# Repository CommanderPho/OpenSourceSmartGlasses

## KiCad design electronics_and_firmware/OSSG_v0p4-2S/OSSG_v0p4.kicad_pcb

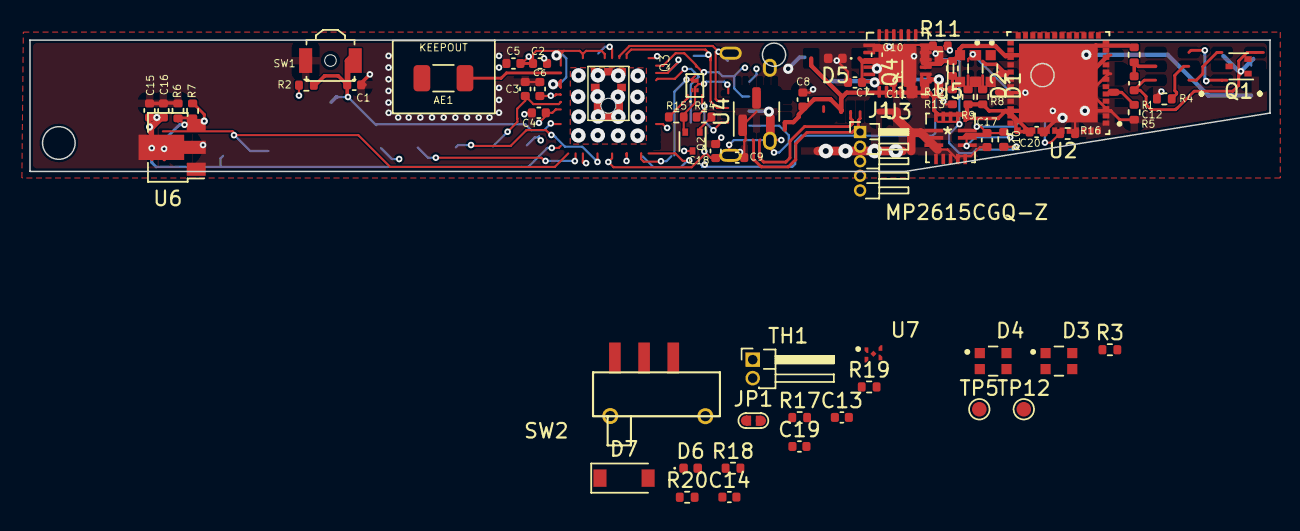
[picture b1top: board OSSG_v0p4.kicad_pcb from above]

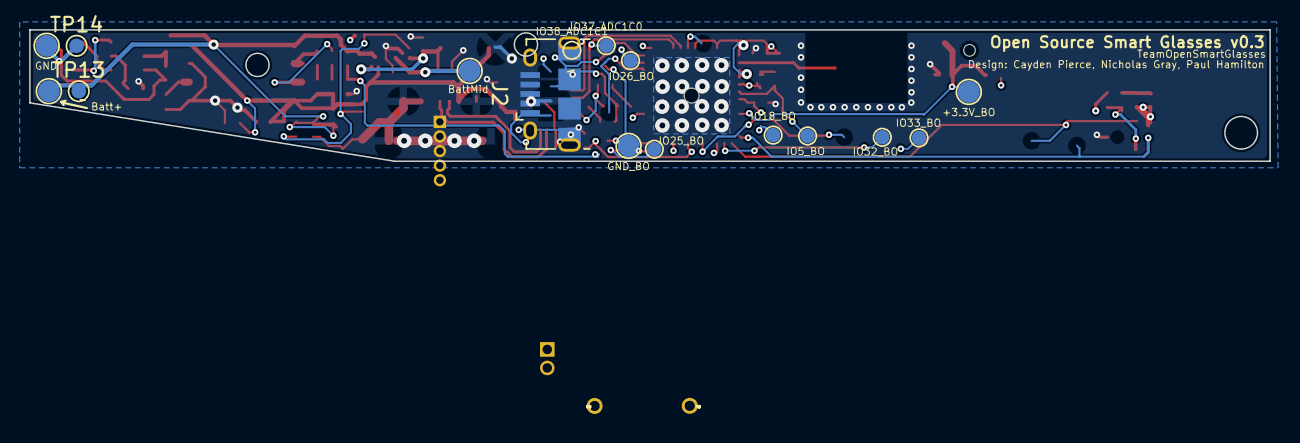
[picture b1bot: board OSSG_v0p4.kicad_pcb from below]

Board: 4 copper layers, 85.0 x 9.0 mm, 82 parts (16 on the bottom side), 54 nets.

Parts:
AE1: ANT3216LL00R2400A
C1, C12: 100nF; C_0402_1005Metric
C2, C9, C17, C19, C20: 1uF; C_0402_1005Metric
C3: 200pF; C_0402_1005Metric
C4, C18: 10uF; C_0402_1005Metric
C5, C6, C7, C8, C10, C11: 0.1uF; C_0402_1005Metric
C13, C14: 1uF/16V; C_0402_1005Metric
C15: 100nF/16V; C_0402_1005Metric
C16: 22uF/16V; C_0402_1005Metric
D1, D2, D3, D4: WS2812C-2020; LED_WS2812C-2020
D5, D6: LED; D_0402_1005Metric
D7: RB160M-30; D_SOD-123
J1: Conn_01x05_Male; PinHeader_1x05_P1.00mm_Horizontal
J2: USB_B_Micro; USB_Micro-B_Amphenol_10118194_Horizontal
JP1: SolderJumper_2_Open; JUMPER-2Psml_Open_RoundedPad2x1mm
Q1, Q2: 2SC4617R BR; SOT-523
Q3: PMZ290UNE2YL; DFN100X60X40-3N
Q4: EMF20B02V; SOT-23-6
R1, R2: 0R*; R_0402_1005Metric
R3, R4, R5, R7: 10K; R_0402_1005Metric
R6: 100k; R_0402_1005Metric
R8, R9: 2K; R_0402_1005Metric
R10, R18, R20: 100K; R_0402_1005Metric
R11, R12: 442K; R_0402_1005Metric
R13, R14: 160K; R_0402_1005Metric
R15, R19: 884K; R_0402_1005Metric
R16: 320K; R_0402_1005Metric
R17: .025; R_0402_1005Metric
SW1: SW_SPST; SW_SPST_B3U-3000P-B
SW2: Power; SW_SMD_SPDT_Slide_9x6.9-hole
TH1: 10K; PinHeader_1x02_P1.27mm_Horizontal
TP1: IO25_BO; Breakout_pads_small
TP2: IO26_BO; Breakout_pads_small
TP3: IO38_ADC1C1; Breakout_pads_small
TP4: IO37_ADC1C0; Breakout_pads_small
TP5: EN_TP; TestPoint_Pad_D1.0mm
TP6: IO32_BO; Breakout_pads_small
TP7: IO33_BO; Breakout_pads_small
TP8: +3.3V_BO; Breakout_pads
TP9: GND_BO; Breakout_pads
TP10: IO5_BO; Breakout_pads_small
TP11: IO18_BO; Breakout_pads_small
TP12: IO0_TP; TestPoint_Pad_D1.0mm
TP13: TXIN; TestPoint_Pad_D1.0mm
TP14: RXIN; TestPoint_Pad_D1.0mm
TP15: Batt+; Breakout_pads
TP16: GND; Breakout_pads
TP17: BattMid; Breakout_pads
U1: SPH0645LMH; SPH0645LM4H-B-SMD-GND
U2: ESP32-PICO-D4; ESP32_PICO_D4
U3: CH9102F; QFN-24-1EP_4x4mm_P0.5mm_EP2.6x2.6mm
U4: XC61CC3002MR; SOT-23
U5: MP2615CGQ-Z; MP2615GQ-P
U6: H7650-50PR; SOT-89-3
U7: NCP167BMX330TBG; REG_NCP167BMX330TBG

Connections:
+3V3: C1.1, C3.2, C11.1, C20.2, J1.1, R1.2, R3.2, TP8.1, U1.5 (VDD), U2.1 (VDDA), U2.3 (VDDA3P3), U2.4 (VDDA3P3), U2.19 (VDD3P3_RTC), U2.37 (VDD3P3_CPU), U2.43 (VDDA), U2.46 (VDDA), U3.5 (VIO), U7.1 (OUT)
+5V: C18.1, D1.4 (VDD), D2.4 (VDD), D3.4 (VDD), D4.4 (VDD), U6.3 (Vout), U7.3 (EN), U7.4 (IN)
ADC1C0: C6.1, TP4.1, U2.6 (SENSOR_CAPP)
ADC1C1: C7.1, TP3.1, U2.7 (SENSOR_CAPN)
ADC1C2: C8.1, R12.2, R13.1, R15.2, R16.1, U2.5 (SENSOR_VP)
BATT1-: C12.1, R6.1, TP17.1, U4.3 (VIN)
BATT2-: C1.2, C2.2, C3.1, C4.2, C5.2, C6.2, C7.2, C8.2, C9.1, C10.2, C11.2, C12.2, C13.2, C14.2, C16.2, C17.2, C18.2, C19.1, C20.1, D1.2 (GND), D2.2 (GND), D3.2 (GND), D4.2 (GND), J1.2, J2.5 (GND), J2.6 (Shield), JP1.2 (B), Q3.2 (S), R2.1, R10.1, R14.2, R16.2, R18.1, R20.1, SW1.1 (A), SW2.1 (A), TH1.2, TP9.1, TP16.1, U1.3 (GND), U2.49 (GND), U3.2 (GND), U3.25 (GND), U4.2 (GND/VSS), U5.8 (AGND), U5.16 (PGND), U6.1 (GND), U7.2 (GND), U7.5 (EXP)
BATT+: C16.1, Q4.1 (S2), R11.1, R15.1, R17.2, R19.2, TP15.1, U5.9 (BATT)
DTR: Q2.2 (E), R4.1, U3.23 (~DTR)
EN: C2.1, Q1.3 (C), R3.1, SW1.2 (B), TP5.1, U2.9 (EN)
IO0: Q2.3 (C), TP12.1, U2.23 (IO0)
IO4: D1.3 (Din), U2.24 (IO4)
IO5: TP10.1, U2.34 (IO5)
IO9: J1.5, U2.28 (SD2)
IO14: U1.6 (Dout), U2.17 (IO14)
IO18: TP11.1, U2.35 (IO18)
IO21: J1.3, U2.42 (IO21)
IO23: J1.4, U2.36 (IO23)
IO25: TP1.1, U2.14 (IO25)
IO26: TP2.1, U2.15 (IO26)
IO32: TP6.1, U1.4 (BCLK), U2.12 (IO32)
IO33: TP7.1, U1.1 (WS), U2.13 (IO33)
unnamed: AE1.2 (PCB_Trace), U2.2 (LNA_IN)
unnamed: C4.1, C5.1
unnamed: C10.1, U3.6 (V3)
unnamed: C13.1, R7.1, TH1.1, U5.13 (NTC)
unnamed: C14.1, U5.14 (TMR)
unnamed: C15.1, U5.15 (BST)
unnamed: C15.2, U5.1 (SW)
unnamed: D1.1 (Dout), D2.3 (Din)
unnamed: D2.1 (Dout), D3.3 (Din)
unnamed: D3.1 (Dout), D4.3 (Din)
unnamed: D5.1 (K), R9.1
unnamed: D6.1 (K), R8.1
unnamed: JP1.1 (A), U5.4 (CELL)
unnamed: R17.1, U5.10 (CSP)
unnamed: Q1.1 (B), R4.2
unnamed: Q2.1 (B), R5.2
unnamed: Q3.3 (D), Q4.2 (G2), R19.1
unnamed: R1.1, R2.2, U1.2 (SEL)
unnamed: R7.2, U5.3 (VCC)
unnamed: R8.2, U5.12 (~AOK)
unnamed: R9.2, U5.11 (~CHGOK)
unnamed: R10.2, U5.6 (~EN)
unnamed: R11.2, R12.1
unnamed: R13.2, R14.1
PSEN: Q3.1 (G), R6.2, R18.2, SW2.2 (B), U4.1 (VOUT)
RTS: Q1.2 (E), R5.1, U3.19 (~RTS)
RX_ESP: TP14.1, U2.40 (U0RXD), U3.21 (TXD)
TX_ESP: TP13.1, U2.41 (U0TXD), U3.20 (RXD)
USB+: J2.3 (D+), U3.3 (UD+)
USB-: J2.2 (D-), U3.4 (UD-)
V_PSU: C17.1, C19.2, D7.1 (K), Q4.3 (S2), U6.2 (Vin)
V_USB: C9.2, D5.2 (A), D6.2 (A), D7.2 (A), J2.1 (VBUS), Q4.4 (G2), R20.2, U3.7 (VDD5), U3.8 (VBUS), U5.2 (Vin)

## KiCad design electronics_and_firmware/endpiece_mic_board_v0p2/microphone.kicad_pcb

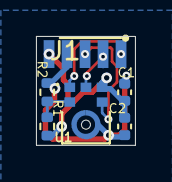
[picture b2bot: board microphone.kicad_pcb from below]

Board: 2 copper layers, 5.5 x 6.0 mm, 7 parts (6 on the bottom side), 6 nets.

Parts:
C1: 100nF/C0G; C_0402_1005Metric
C2: 1uF/C0G; C_0402_1005Metric
G1: Microphone_Graphic; Microhone_Graphic_sml
J1: I2S_MIC_EXT; Solder-5P-Connector
R1, R2: 0R*; R_0402_1005Metric
U1: SPH0645LMH; MIC_SPH0645LM4H-B

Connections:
+3V3: C1.1, C2.1, J1.5, R1.1, U1.5 (VDD)
GND: C1.2, C2.2, J1.4, R2.2, U1.3 (GND)
unnamed: J1.1, U1.1 (WS)
unnamed: J1.2, U1.6 (Dout)
unnamed: J1.3, U1.4 (BCLK)
unnamed: R1.2, R2.1, U1.2 (SEL)

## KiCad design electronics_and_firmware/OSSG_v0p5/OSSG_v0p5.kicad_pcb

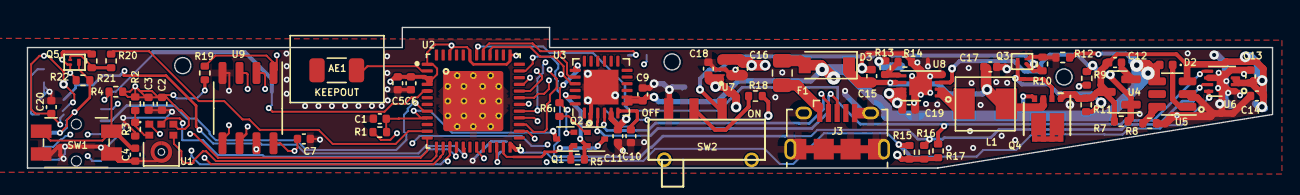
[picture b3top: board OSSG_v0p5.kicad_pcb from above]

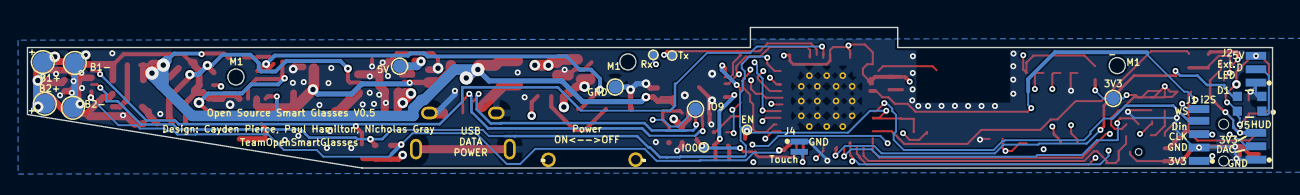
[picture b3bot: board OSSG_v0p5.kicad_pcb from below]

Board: 4 copper layers, 93.0 x 10.5 mm, 80 parts (17 on the bottom side), 53 nets.

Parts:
AE1: ANT3216LL00R2400A
C1, C9, C15, C18, C20: 1uF; C_0402_1005Metric
C2, C4, C6, C7, C10, C11, C12, C13, C16: 100nF; C_0402_1005Metric
C3: 200pF; C_0402_1005Metric
C5: 10uF; C_0402_1005Metric
C14, C17, C19: 22uF; C_0402_1005Metric
D1: WS2812B-2020; LED_WS2812C-2020
D2: Red; D_0402_1005Metric
D3: RB160M-30; D_SOD-123
F1: 1A; R_0805_2012Metric
J1: Conn_01x05_Male; Solder-5P-Connector
J2: Ext RGB; Solder-3P-Connector
J3: USB_B_Micro; USB_Micro-B_Amphenol_10118194_Horizontal
J4: Touch; Solder-2P-Connector
J5: Ext. HUD; Solder-3P-Connector
L1: 1.5uH; 1.5uH_YXMAA0402-1R5M-ANP
Q1, Q2: 2SC4617R BR; SOT-523
Q3: PMZ290UNE2YL; DFN100X60X40-3N
Q4: YJQD30P02A; YJQD30P02A_DFN3.3x3.3
Q5: PMZ350UPEYL; DFN100X60X40-3N
R1, R4, R5, R6, R17, R18, R20: 10K; R_0402_1005Metric
R2, R3: 0R*; R_0402_1005Metric
R7, R10, R21: 100K; R_0402_1005Metric
R8: 2.1k; R_0402_1005Metric
R9: 150; R_0402_1005Metric
R11, R12: 1M; R_0402_1005Metric
R13: 470K; R_0402_1005Metric
R14: 147K; R_0402_1005Metric
R15, R16: 4.7K; R_0402_1005Metric
R19: *10k; R_0402_1005Metric
R22: NC; R_0402_1005Metric
SW1: SW_SPST; SMD_Switch_Panasonic_EVQPUL_EVQPUC_6.3x6.7
SW2: Power; SW_SMD_SPDT_Slide_9x6.9-hole
TP1: IO9; Breakout_pads_small
TP2: 5V; Breakout_pads_small
TP5: EN; Breakout_pads_very_small
TP8: 3V3; Breakout_pads_small
TP9: GND; Breakout_pads_small
TP12: IO0; Breakout_pads_very_small
TP13: Tx; Breakout_pads_very_small
TP14: Rx; Breakout_pads_very_small
TP15: Batt1+; Breakout_pads
TP16: Batt2+; Breakout_pads
TP17: BATT1-; Breakout_pads
TP18: BATT2-; Breakout_pads
U1: SPH0645LMH; MIC_SPH0645LM4H-B
U2: ESP32-PICO-D4; ESP32_PICO_D4_PQFN50P700X700X104-49N
U3: CH9102F; QFN-24-1EP_4x4mm_P0.5mm_EP2.6x2.6mm
U4: XC61CC3002MR; SOT-23
U5: AP5054HTC; SOT-23-6
U6: MAX17048; DFN-8-1EP_2x2mm_P0.5mm_EP0.8x1.6mm
U7: NCP167BMX330TBG; REG_NCP167BMX330TBG
U8: SY7088; DFN-8-1EP_3x2mm_P0.5mm_EP1.7x1.4mm
U9: LY68L6400SLIT_PSRAM; SOP-8_3.9x4.9mm_P1.27mm

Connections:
+3V3: C2.1, C3.2, C5.1, C6.1, C11.1, C18.2, J1.1, Q5.2 (S), R1.2, R2.2, R4.2, R15.1, R16.1, R17.1, R19.1, R21.2, R22.2, TP8.1, U1.5 (VDD), U2.1 (VDDA), U2.3 (VDDA3P3), U2.4 (VDDA3P3), U2.19 (VDD3P3_RTC), U2.37 (VDD3P3_CPU), U2.43 (VDDA), U2.46 (VDDA), U3.5 (VIO), U7.1 (OUT)
+5V: C16.1, C19.1, C20.1, D1.4 (VDD), J2.3, R13.2, TP2.1, U7.3 (EN), U7.4 (IN), U8.7 (OUT), U8.8 (OUT)
ALRT: R17.2, U2.42 (IO21), U6.5 (ALRT)
BATT1-: C1.2, C2.2, C3.1, C4.2, C5.2, C6.2, C7.2, C9.1, C10.2, C11.2, C12.2, C13.2, C14.2, C15.2, C16.2, C17.2, C18.1, C19.2, C20.2, D1.2 (GND), J1.2, J2.1, J3.5 (GND), J3.6 (Shield), J4.1, J5.1, Q3.2 (S), R3.1, R8.1, R10.1, R12.1, R14.1, SW1.2 (B), SW2.1 (A), TP9.1, TP17.1, TP18.1, U1.3 (GND), U2.49 (GND), U3.2 (GND), U3.25 (GND), U4.2 (GND/VSS), U5.2 (GND), U6.1 (CTG), U6.4 (GND), U6.6 (QSTRT), U6.9 (EP), U7.2 (GND), U7.5 (EXP), U8.4 (GND), U8.9 (Pad), U9.4 (Vss)
BATT+: C12.1, C13.1, C14.1, Q4.1 (S2), R7.1, R11.2, R18.1, TP15.1, TP16.1, U4.3 (VIN), U5.3 (BAT), U6.2 (CELL), U6.3 (Vdd)
DAC: J5.2, U2.15 (IO26)
DISPLAY_EN: R20.2, U2.11 (IO35)
DTR: Q2.2 (E), R5.1, U3.23 (~DTR)
EN: C1.1, Q1.3 (C), R1.1, TP5.1, U2.9 (EN)
HUD+: J5.3, Q5.3 (D), R22.1
IO0: Q2.3 (C), TP12.1, U2.23 (IO0)
IO9: TP1.1, U2.28 (SD2)
unnamed: AE1.2 (PCB_Trace), U2.2 (LNA_IN)
unnamed: C10.1, U3.6 (V3)
unnamed: C15.1, C17.1, D3.1 (K), L1.1, Q4.3 (S2), U8.6 (IN)
unnamed: D1.1 (Dout), J2.2
unnamed: D2.1 (K), U5.1 (~CHRG)
unnamed: F1.1, J3.1 (VBUS)
unnamed: L1.2, U8.1 (LX), U8.2 (LX)
unnamed: Q1.1 (B), R5.2
unnamed: Q2.1 (B), R6.2
unnamed: Q3.1 (G), R9.2, R10.2, SW2.2 (B)
unnamed: Q3.3 (D), Q4.2 (G2), R11.1
unnamed: Q4.5 (D2), Q4.6 (D2), Q4.7 (D2), Q4.8 (D2)
unnamed: Q5.1 (G), R20.1, R21.1
unnamed: R2.1, R3.2, U1.2 (SEL)
unnamed: R8.2, U5.6 (PROG)
unnamed: R13.1, R14.2, U8.5 (FB)
unnamed: R18.2, SW2.3 (C)
PSEN: R7.2, R9.1, U4.1 (VOUT), U8.3 (EN)
PSRAM_CS: R19.2, U2.29 (SD3), U9.1 (CE#)
RGB: D1.3 (Din), U2.17 (IO14)
RTS: Q1.2 (E), R6.1, U3.19 (~RTS)
RX_ESP: TP14.1, U2.40 (U0RXD), U3.21 (TXD)
SCL: R16.2, U2.35 (IO18), U6.7 (SCL)
SCLK: U2.31 (CLK), U9.6 (SCLK)
SDA: R15.2, U2.24 (IO4), U6.8 (SDA)
SIO0: U2.33 (SD1), U9.5 (SI/SIO[0])
SIO1: U2.27 (IO17), U9.2 (SO/SIO[1])
SIO2: U2.32 (SD0), U9.3 (SIO[2])
SIO3: U2.30 (CMD), U9.7 (SIO[3])
SWITCH: C4.1, R4.1, SW1.1 (A), U2.5 (SENSOR_VP)
TOUCH1: J4.2, U2.22 (IO2)
TX_ESP: TP13.1, U2.41 (U0TXD), U3.20 (RXD)
USB+: J3.3 (D+), U3.3 (UD+)
USB-: J3.2 (D-), U3.4 (UD-)
VBUS: C9.2, D2.2 (A), D3.2 (A), F1.2, Q4.4 (G2), R12.2, U3.7 (VDD5), U3.8 (VBUS), U5.4 (VCC)
VDD_SDIO: C7.1, U2.26 (VDD_SDIO), U9.8 (Vcc)
i2S1_CLK: U1.4 (BCLK), U2.13 (IO33)
i2S1_Data: U1.6 (Dout), U2.16 (IO27)
i2S2_CLK: J1.3, U2.14 (IO25)
i2S2_Data: J1.4, U2.8 (SENSOR_VN)
i2S2_WS: J1.5, U1.1 (WS), U2.12 (IO32)

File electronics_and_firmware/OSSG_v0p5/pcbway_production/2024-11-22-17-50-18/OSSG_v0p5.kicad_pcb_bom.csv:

Designator,Quantity,Value,Footprint,Package,MPN,DNP,Mount_Type,MPN_LCSC,Price_LCSC,DigiKeyLink,LCSCLink,Price,LinkLCSC,MANUFACTURER,MAXIMUM_PACKAGE_HEIGHT,PARTREV,STANDARD
AE1,1,ANT3216LL00R2400A,ANT3216LL00R2400A,,,,smt,C293767,0.1226,,,,,,,,
"C1, C15, C18, C20, C9",5,1uF,C_0402_1005Metric,,490-GRT155C80J105KE01JCT-ND,,smt,C14445,0.0018,https://www.digikey.ca/en/products/detail/murata-electronics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,https://lcsc.com/product-detail/Multilayer-Ceramic-Capacitor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,0.0448,,,,,
"C10, C11, C12, C2, C7",5,100nF,C_0402_1005Metric,,,,smt,"[C10,C11]C258109; [C12,C2,C7]C41851","[C10,C11]0.0005; [C12]0.0008; [C2,C7]0.0009",,https://lcsc.com/product-detail/Chip-Resistor-Surface-Mount_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,,https://lcsc.com/product-detail/Multilayer-Ceramic-Capacitor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,,,,
"C13, C16, C4",3,100nF,C_0402_1005Metric,,490-GRT155C80J105KE01JCT-ND,,smt,C14445,0.0018,https://www.digikey.ca/en/products/detail/murata-electronics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,https://lcsc.com/product-detail/Multilayer-Ceramic-Capacitor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,0.0448,,,,,
"C14, C17, C19",3,22uF,C_0402_1005Metric,,490-GRT155C80J105KE01JCT-ND,,smt,C14445,0.0018,https://www.digikey.ca/en/products/detail/murata-electronics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,https://lcsc.com/product-detail/Multilayer-Ceramic-Capacitor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,0.0448,,,,,
C3,1,200pF,C_0402_1005Metric,,,,smt,C41851,0.0009,,,,https://lcsc.com/product-detail/Multilayer-Ceramic-Capacitor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,,,,
C5,1,10uF,C_0402_1005Metric,,1276-1450-1-ND,,smt,C15525,0.0057,https://www.digikey.ca/en/products/detail/samsung-electro-me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,https://lcsc.com/product-detail/Multilayer-Ceramic-Capacitor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,0.1092,,,,,
C6,1,100nF,C_0402_1005Metric,,1276-1043-1-ND,,smt,C41851,0.0008,https://www.digikey.ca/en/products/detail/samsung-electro-me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,,0.006,https://lcsc.com/product-detail/Multilayer-Ceramic-Capacitor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,,,,
D1,1,WS2812B-2020,LED_WS2812C-2020,,,,tht,C965555,,,https://lcsc.com/product-detail/Light-Emitting-Diodes-LED_Wo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,,,,,,
D2,1,Red,D_0402_1005Metric,,,,smt,C965790,,,,,,,,,
D3,1,RB160M-30,D_SOD-123,,,,smt,C2937163,0.0743,,,,,,,,
F1,1,1A,R_0805_2012Metric,,,,smt,C2830233,,,,,,,,,
J1,1,Conn_01x05_Male,Solder-5P-Connector,,,,tht,,,,,,,,,,
J2,1,Ext RGB,Solder-3P-Connector,,,,tht,,,,,,,,,,
J3,1,USB_B_Micro,USB_Micro-B_Amphenol_10118194_Horizontal,,WM1399CT-ND,,smt,C136000,0.244,https://www.digikey.ca/en/products/detail/molex/1050170001/2350832,,1.33,https://lcsc.com/product-detail/USB-Connectors_MOLEX-1050170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,,,,
J4,1,Touch,Solder-2P-Connector,,,,tht,,,,,,,,,,
J5,1,Ext. HUD,Solder-3P-Connector,,,,tht,,,,,,,,,,
L1,1,1.5uH,1.5uH_YXMAA0402-1R5M-ANP,,,,tht,C241335,,,,,,,,,
"Q1, Q2",2,2SC4617R BR,SOT-523,,,,smt,C2836080,0.0163,,https://lcsc.com/product-detail/Bipolar-Transistors-BJT_CBI-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,,,,,,
Q3,1,PMZ290UNE2YL,DFN100X60X40-3N,,,,tht,C478155,,,,,,,,,
Q4,1,YJQD30P02A,YJQD30P02A_DFN3.3x3.3,,,,tht,C919546,,,,,,,,,
Q5,1,PMZ350UPEYL,DFN100X60X40-3N,,,,tht,C478207,0.0804,,,,,,,,
"R1, R4, R5, R6",4,10K,R_0402_1005Metric,,RMCF0402JT10K0CT-ND,,smt,C2906885,0.0005,https://www.digikey.ca/en/products/detail/stackpole-electron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,https://lcsc.com/product-detail/Chip-span-style-background-c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,0.018,,,,,
"R10, R21, R7",3,100K,R_0402_1005Metric,,,,smt,"[R10,R21]1; [R7]C106234",0.0005,,,,,,,,
"R11, R12",2,1M,R_0402_1005Metric,,,,smt,C2906900,0.0004,,,,,,,,
R13,1,470K,R_0402_1005Metric,,,,smt,C25562,0.0004,,,,,,,,
R14,1,147K,R_0402_1005Metric,,,,smt,C2933073,0.0005,,,,,,,,
"R15, R16",2,4.7K,R_0402_1005Metric,,,,smt,C106234,0.0005,,,,,,,,
"R17, R18, R20",3,10K,R_0402_1005Metric,,,,smt,"[R17]C106234; [R18,R20]1",0.0005,,,,,,,,
R19,1,*10k,R_0402_1005Metric,,,,smt,C2906885,,,,,,,,,
"R2, R3",2,0R*,R_0402_1005Metric,,,,smt,C2906877,0.0004,https://www.digikey.ca/en/products/detail/stackpole-electron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,,[R2]0.004; [R3]0.0004,,,,,
R22,1,NC,R_0402_1005Metric,,,,smt,C2906877,0.0004,https://www.digikey.ca/en/products/detail/stackpole-electron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,https://lcsc.com/product-detail/Chip-span-style-background-c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,0.0004,,,,,
R8,1,2.1k,R_0402_1005Metric,,,,smt,C100301,0.0006,,,,,,,,
R9,1,150,R_0402_1005Metric,,,,smt,C106234,0.0005,,,,,,,,
SW1,1,SW_SPST,SMD_Switch_Panasonic_EVQPUL_EVQPUC_6.3x6.7,,UK-B0249-SP25Y,,smt,C493280,,https://www.digikey.ca/en/products/detail/omron-electronics-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,,,,,,,
SW2,1,Power,SW_SMD_SPDT_Slide_9x6.9-hole,,,,tht,C145858,,,,,,,,,
TP1,1,IO9,Breakout_pads_small,,,,smt,,,,,,,,,,
TP12,1,IO0,Breakout_pads_very_small,,,,smt,,,,,,,,,,
TP13,1,Tx,Breakout_pads_very_small,,,,smt,,,,,,,,,,
TP14,1,Rx,Breakout_pads_very_small,,,,smt,,,,,,,,,,
TP15,1,Batt1+,Breakout_pads,,,,smt,,,,,,,,,,
TP16,1,Batt2+,Breakout_pads,,,,smt,,,,,,,,,,
TP17,1,BATT1-,Breakout_pads,,,,smt,,,,,,,,,,
TP18,1,BATT2-,Breakout_pads,,,,smt,,,,,,,,,,
TP2,1,5V,Breakout_pads_small,,,,smt,,,,,,,,,,
TP5,1,EN,Breakout_pads_very_small,,,,smt,,,,,,,,,,
TP8,1,3V3,Breakout_pads_small,,,,smt,,,,,,,,,,
TP9,1,GND,Breakout_pads_small,,,,smt,,,,,,,,,,
U1,1,SPH0645LMH,MIC_SPH0645LM4H-B,,,,tht,,,,,,,,,,
U2,1,ESP32-PICO-D4,ESP32_PICO_D4_PQFN50P700X700X104-49N,,1904-1029-1-ND,,tht,C193707,,https://www.digikey.ca/en/products/detail/espressif-systems/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,https://lcsc.com/product-detail/RF-Transceiver-ICs_Espressif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,4.1837,,Espressif Systems,1.04 mm,v1.9,IPC 7351B
U3,1,CH9102F,QFN-24-1EP_4x4mm_P0.5mm_EP2.6x2.6mm,,,,smt,C2858418,1.35,,,,,,,,
U4,1,XC61CC3002MR,SOT-23,,,,smt,C80698,0.1688,,,,,,,,
U5,1,AP5054HTC,SOT-23-6,,,,smt,C2843820,,,https://www.lcsc.com/product-detail/Battery-Management-ICs_W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,,,,,,
U6,1,MAX17048,DFN-8-1EP_2x2mm_P0.5mm_EP0.8x1.6mm,,,,smt,C2682616,0.9912,,,,,,,,
U7,1,NCP167BMX330TBG,REG_NCP167BMX330TBG,,,,tht,C892227,0.4418,,,,,ON Semiconductor,0.43mm,3,Manufacturer recommendations
U8,1,SY7088,DFN-8-1EP_3x2mm_P0.5mm_EP1.7x1.4mm,,,,smt,C178240,,,,,,,,,
U9,1,LY68L6400SLIT_PSRAM,SOP-8_3.9x4.9mm_P1.27mm,,,,smt,C261881,,,https://www.lcsc.com/product-detail/RAM_Lyontek-Inc-LY68L640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,,,,,,

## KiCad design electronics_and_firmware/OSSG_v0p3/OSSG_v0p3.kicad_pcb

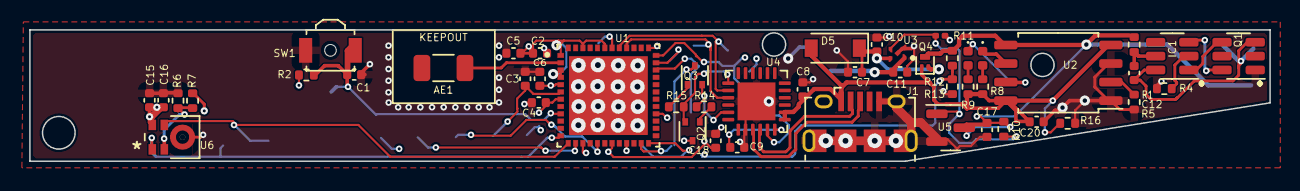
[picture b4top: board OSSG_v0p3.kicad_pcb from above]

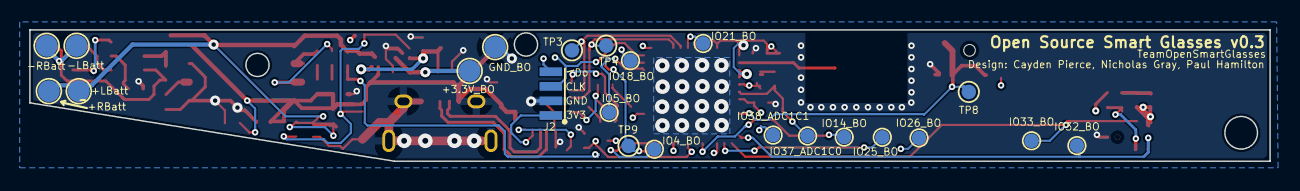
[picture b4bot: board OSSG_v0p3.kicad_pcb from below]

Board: 4 copper layers, 85.0 x 9.0 mm, 71 parts (22 on the bottom side), 44 nets.

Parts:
AE1: ANT3216LL00R2400A
C1, C7, C8, C10, C11: 1uF; C_0402_1005Metric
C2: 10uF; C_0402_1005Metric
C3, C4, C5, C6, C9, C17, C18, C20: 0.1uF; C_0402_1005Metric
C12: 100nF; C_0402_1005Metric
C15: 100nF/C0G; C_0402_1005Metric
C16: 1uF/C0G; C_0402_1005Metric
D1, D2: LED; D_0402_1005Metric
D5: RB160M-30; D_SOD-123
IC1: DW01A; SOT-23-6
J1: USB_B_Micro; USB_Micro-B_Amphenol_10118194_Horizontal
J2: External PDM Mic Input; Solder-4P-Connector
Q1: FS8205A; SOT-23-6
Q2, Q3: Q_NPN_BEC; SOT-523
Q4: Q_PMOS_GSD; SOT-883
R1: 100; R_0402_1005Metric
R2, R14, R15: 10K; R_0402_1005Metric
R4: 1K; R_0402_1005Metric
R5: 4K; R_0402_1005Metric
R6, R7: 10K*; R_0402_1005Metric
R8, R9: 1k; R_0402_1005Metric
R10, R16: 100k; R_0402_1005Metric
R11: NC; R_0201_0603Metric
R12: 442K; R_0402_1005Metric
R13: 160K; R_0402_1005Metric
SW1: SW_SPST; SW_SPST_B3U-3000P-B
TP1: IO4_BO; Breakout_pads_small
TP2: IO18_BO; Breakout_pads_small
TP3: TXIN; TestPoint_Pad_D1.0mm
TP4: RXIN; TestPoint_Pad_D1.0mm
TP6: IO25_BO; Breakout_pads_small
TP7: IO26_BO; Breakout_pads_small
TP8: EN_TP; TestPoint_Pad_D1.0mm
TP9: IO0_TP; TestPoint_Pad_D1.0mm
TP10: IO37_ADC1C0; Breakout_pads_small
TP11: IO38_ADC1C1; Breakout_pads_small
TP13: +LBatt; Breakout_pads
TP14: -LBatt; Breakout_pads
TP15: +RBatt; Breakout_pads
TP16: -RBatt; Breakout_pads
TP17: +3.3V_BO; Breakout_pads
TP18: GND_BO; Breakout_pads
TP19: IO21_BO; Breakout_pads_small
TP20: IO14_BO; Breakout_pads_small
TP21: IO5_BO; Breakout_pads_small
TP22: IO32_BO; Breakout_pads_small
TP24: IO33_BO; Breakout_pads_small
U1: ESP32-PICO-D4; ESP32_PICO_D4
U2: TP4056; SOP-8_5.28x5.23mm_P1.27mm
U3: NCP167BMX330TBG; REG_NCP167BMX330TBG
U4: CH9102F; QFN-24-1EP_4x4mm_P0.5mm_EP2.6x2.6mm
U5: XC61CC3002MR; SOT-23
U6: MP23DB01HPTR

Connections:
+3.3VA: C2.1, C5.1, U1.1 (VDDA), U1.3 (VDDA3P3), U1.4 (VDDA3P3), U1.43 (VDDA), U1.46 (VDDA)
+3V3: C11.2, C15.2, C16.2, C18.1, J2.1, R2.2, R6.2, TP17.1, U1.19 (VDD3P3_RTC), U1.37 (VDD3P3_CPU), U3.1 (OUT), U4.5 (VIO), U6.5 (VDD)
ADC1C0: C3.1, TP10.1, U1.6 (SENSOR_CAPP)
ADC1C1: C4.1, TP11.1, U1.7 (SENSOR_CAPN)
ADC1C2: C6.1, R12.2, R13.1, U1.5 (SENSOR_VP)
BATT+: C17.1, Q4.3 (D), R1.1, R10.1, R12.1, TP13.1, TP15.1, U2.5 (BAT), U5.3 (VIN)
BATT-: C12.2, IC1.6 (GND), Q1.3 (S2), TP14.1, TP16.1
DTR: Q3.2 (E), R14.1, U4.23 (~DTR)
EN: C1.1, Q2.3 (C), R2.1, SW1.2 (B), TP8.1, U1.9 (EN)
EXT1_MIC_CLK: J2.3, U1.36 (IO23)
EXT1_MIC_DATA: J2.4, U1.28 (SD2)
GND: C1.2, C2.2, C3.2, C4.2, C5.2, C6.2, C7.1, C8.1, C9.2, C10.1, C11.1, C15.1, C16.1, C17.2, C18.2, C20.2, J1.5 (GND), J1.6 (Shield), J2.2, Q1.1 (S1), R4.2, R5.1, R7.1, R13.2, R16.1, SW1.1 (A), TP18.1, U1.49 (GND), U2.1 (TEMP), U2.3 (GND), U3.2 (GND), U3.5 (EXP), U4.2 (GND), U4.25 (GND), U5.2 (GND/VSS), U6.3 (GND)
IO0: Q3.3 (C), TP9.1, U1.23 (IO0)
IO4: TP1.1, U1.24 (IO4)
IO5: TP21.1, U1.34 (IO5)
IO14: TP20.1, U1.17 (IO14)
IO18: TP2.1, U1.35 (IO18)
IO21: TP19.1, U1.42 (IO21)
IO25: TP6.1, U1.14 (IO25)
IO26: TP7.1, U1.15 (IO26)
IO32: TP22.1, U1.12 (IO32), U6.1 (DOUT)
IO33: TP24.1, U1.13 (IO33), U6.4 (CLK)
unnamed: AE1.2 (PCB_Trace), U1.2 (LNA_IN)
unnamed: C9.1, U4.6 (V3)
unnamed: C12.1, IC1.5 (VCC), R1.2
unnamed: D1.1 (K), U2.6 (~STDBY)
unnamed: D1.2 (A), R8.2
unnamed: D2.1 (K), U2.7 (~CHRG)
unnamed: D2.2 (A), R9.2
unnamed: IC1.1 (OD), Q1.4 (G2)
unnamed: IC1.2 (CS), R4.1
unnamed: IC1.3 (OC), Q1.6 (G1)
unnamed: Q2.1 (B), R14.2
unnamed: Q3.1 (B), R15.2
unnamed: R5.2, U2.2 (PROG)
unnamed: R6.1, R7.2, U6.2 (L/R)
PSEN: R10.2, R11.1, U3.3 (EN), U5.1 (VOUT)
RTS: Q2.2 (E), R15.1, U4.19 (~RTS)
RX_ESP: TP4.1, U1.40 (U0RXD), U4.21 (TXD)
TX_ESP: TP3.1, U1.41 (U0TXD), U4.20 (RXD)
USB+: J1.3 (D+), U4.3 (UD+)
USB-: J1.2 (D-), U4.4 (UD-)
V_PSU: C7.2, C10.2, D5.1 (K), Q4.2 (S), R11.2, U3.4 (IN)
V_USB: C8.2, C20.1, D5.2 (A), J1.1 (VBUS), Q4.1 (G), R8.1, R9.1, R16.2, U2.4 (VCC), U2.8 (CE), U4.7 (VDD5), U4.8 (VBUS)

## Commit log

2024-11-27 generated stuff
